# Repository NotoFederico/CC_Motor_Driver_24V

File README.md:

# Driver para motor de corriente continua

Sistema operativo: Windows / Software: KICAD

Circuito impreso realizado en KICAD que implementa en su diseño un medio puente H con transistores MOSFET para el control de un motor de corriente continua de 24V con aplicación en un ambiente industrial

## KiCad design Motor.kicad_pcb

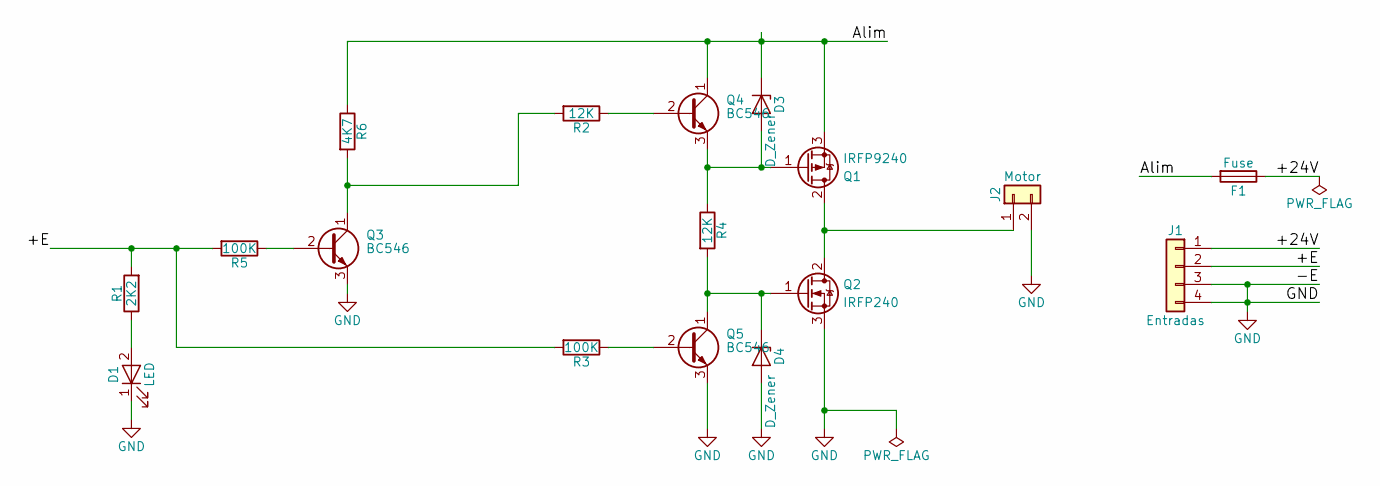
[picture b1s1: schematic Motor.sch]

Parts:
D1: LED; LED_D5.0mm
D3, D4: D_Zener; D_DO-41_SOD81_P12.70mm_Horizontal
F1: Fuse; Fuseholder5x20_horiz_open_Schurter_0031_8201
J1: Entradas; AK300-4
J2: Motor; AK300-2
Q1: IRFP9240; TO-247_TO-3P_Vertical
Q2: IRFP240; TO-247_TO-3P_Vertical
Q3, Q4, Q5: BC546; TO-92_Inline_Wide
R1: 2K2; R_Axial_DIN0309_L9.0mm_D3.2mm_P12.70mm_Horizontal
R2, R4: 12K; R_Axial_DIN0309_L9.0mm_D3.2mm_P12.70mm_Horizontal
R3, R5: 100K; R_Axial_DIN0309_L9.0mm_D3.2mm_P12.70mm_Horizontal
R6: 4K7; R_Axial_DIN0309_L9.0mm_D3.2mm_P12.70mm_Horizontal

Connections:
/+24V: F1.1, J1.1
/+E: J1.2, R1.2, R3.2, R5.2
/Alim: D3.1 (K), F1.2, Q1.3 (S), Q4.1 (C), R6.1
GND: D1.1 (K), D4.2 (A), J1.3, J1.4, J2.2, Q2.3 (S), Q3.3 (E), Q5.3 (E)
unnamed: D1.2 (A), R1.1
unnamed: D3.2 (A), Q1.1 (G), Q4.3 (E), R4.1
unnamed: D4.1 (K), Q2.1 (G), Q5.1 (C), R4.2
unnamed: J2.1, Q1.2 (D), Q2.2 (D)
unnamed: Q3.1 (C), R2.2, R6.2
unnamed: Q3.2 (B), R5.1
unnamed: Q4.2 (B), R2.1
unnamed: Q5.2 (B), R3.1

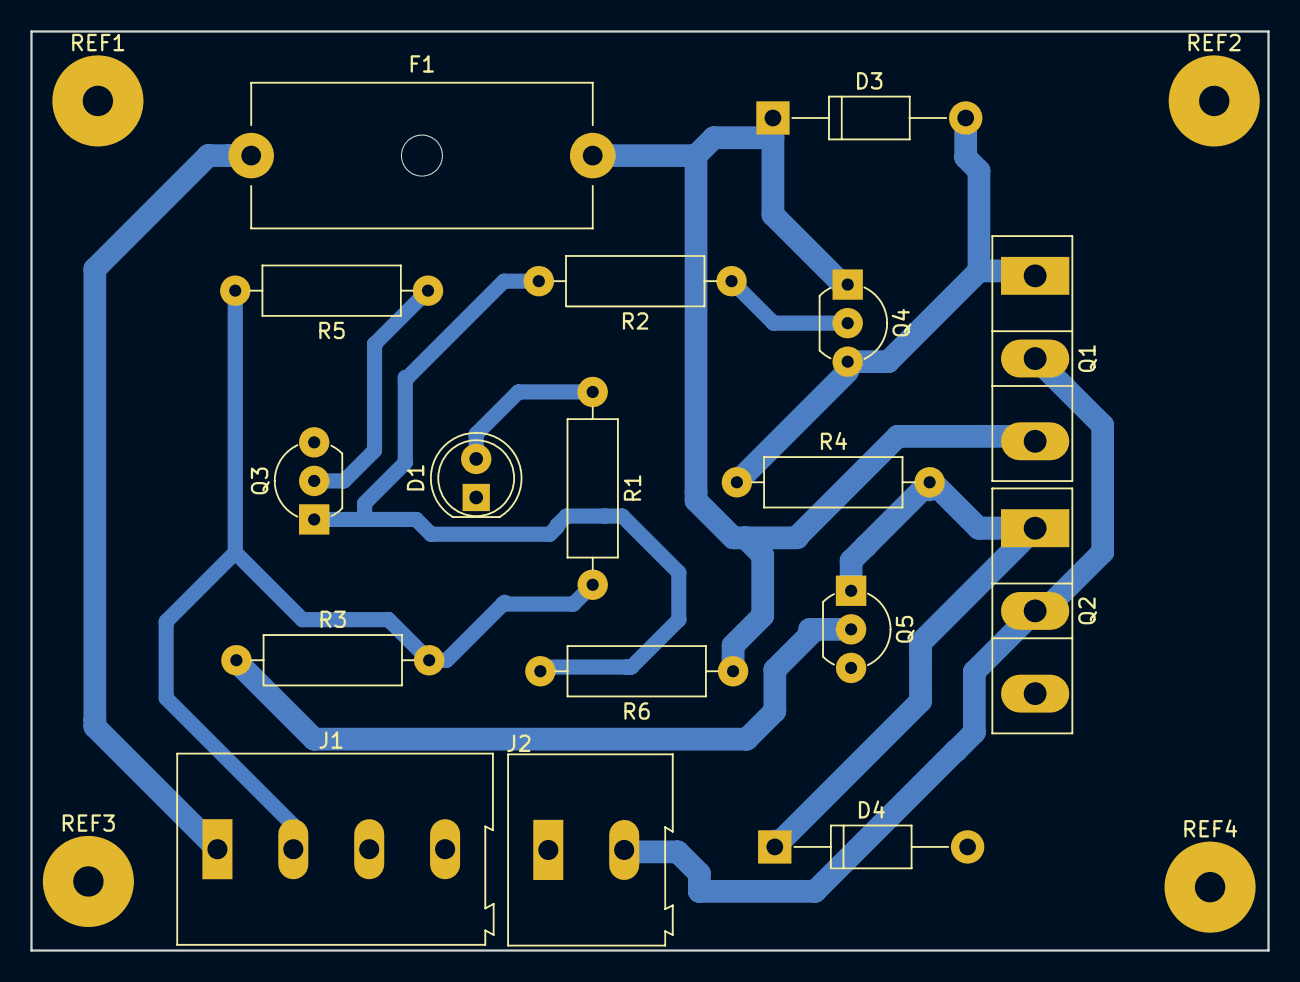
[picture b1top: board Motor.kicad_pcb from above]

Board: 2 copper layers, 81.5 x 60.5 mm, 21 parts (0 on the bottom side), 12 nets.

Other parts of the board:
REF1, REF2, REF3, REF4: SolderWirePad_single_1mmDrill
